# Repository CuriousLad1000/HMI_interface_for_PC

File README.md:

# HMI interface for PC

## Introduction

Personal Computers have become an integral part of our lives that even thinking about living without one would give us the feeling of falling back into stone age.

The idea behind this project was to build a smart Human Machine Interface for my personal computer. This project provided me with the opportunity of honing my skills while exploring various other domains. This project required technical expertise from different fields of technology including Electronics, Computer Science and Mechanical.

## Project Objective

The HMI interface will provide some advanced functionalities such as auto boot and shutdown, Automatic Temperature controller, vent controller, Lighting controller etc…

The project will involve some custom hardware designing, PCB fabrication, UX Designing, firmware programming, some mechanical designing and assembly using Rapid prototyping machines.

## Hardware/components used (not exhaustive list)

-   Arduino MEGA
-   3.5-inch Touch panel from Nextion
-   DC to DC Buck-Boost drivers
-   Mosfets (IRF510)
-   various passive components
-   Acryllic and MDF for casing and PC cabinet casing.
-   Laser cutter
-   CNC milling machine

## Software used

-   Arduino IDE (C/C++)
-   Nextion Editor to program touch panel.
-   Adobe Photoshop for UI designing.
-   Corel draw for Case, side panel and vents designing.
-   Cadsoft Eagle for PCB designing
-   Roland’s software and artcam for PCB fabrication (CNC milling).

##  Features offered

After completion, the HMI interface will have the following features.

-   Provide interactive system on/off switch
-   System Power on scheduler
-   Control the speed of fan based on conditions set.
    -   manual control of fan speed
    -   Automatic control based on the component’s temperature
-   Different Lighting modes for the system across multiple channels
    -   Rainbow
    -   Single color
    -   Fading on single color
    -   Rainbow cycle
    -   Color based on temperature
-   Display current temperature on multiple temperature gauges.
-   Provide settings for additional functionalities such as
    -   Open vents when system boots or based on the temperature -- servo control
    -   Enable power saver
    -   Enable/disable system status LED.
    -   Temperature channel assignment to various components.

<br/>

## Sample pictures (refer to wiki for more…)

<br/>

### HMI Interface

<br/>

**Home screen**

<p align="Center"> <i>"note: logo copyright belongs to Micro-Star INT'L CO., LTD" </i></p>

<br/>
<br/>

**Set Lighting modes**

<br/>
<br/>

**Temperature monitor**

<br/>
<br/>

## Device pics

<br/>
<br/>

**HMI Installed**

<br/>
<br/>

**HMI Operational**

<br/>
<br/>

> Check out wiki for more pics

<br/>
<br/>

### Video

<br/>
<br/>

**Device in action part-1**

<br/>
<br/>

**Device in action part-2**

<br/>

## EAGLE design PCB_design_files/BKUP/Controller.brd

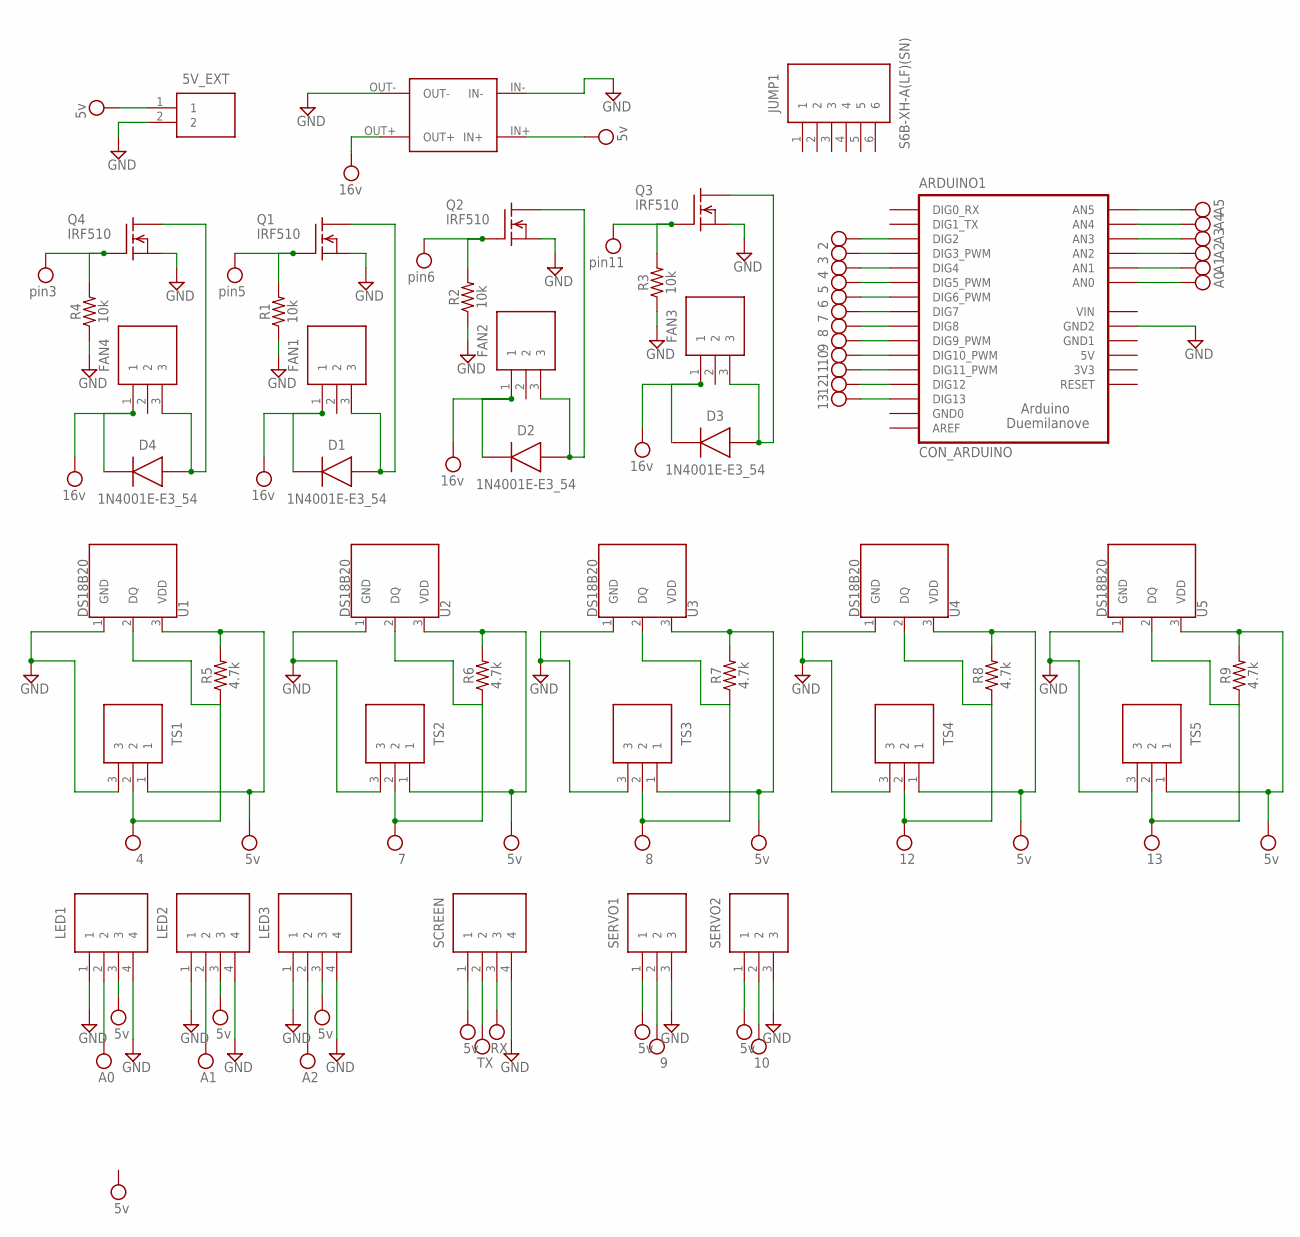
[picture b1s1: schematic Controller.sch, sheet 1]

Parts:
5V_EXT: S2B-XH-A(LF)(SN); SHDR2W80P0X250_1X2_740X575X700
ARDUINO1: CON_ARDUINO
D1, D2, D3, D4: 1N4001E-E3_54; DIOAD1405W86L465D235
FAN1, FAN2, FAN3, FAN4: S3B-XH-A(LF)(SN); SHDR3W80P0X250_1X3_990X610X700
JUMP1: S6B-XH-A(LF)(SN); SHDR6W64P0X250_1X6_1740X1155X7
LED1, LED2, LED3: S4B-XH-A(LF)(SN); SHDR4W64P0X250_1X4_1240X1155X7
Q1, Q2, Q3, Q4: IRF510; TO220
R1, R2, R3, R4: 10k; AXIAL-0.3
R5, R6, R7, R8, R9: 4.7k; AXIAL-0.3
SCREEN: S4B-XH-A(LF)(SN); SHDR4W64P0X250_1X4_1240X1155X7
SERVO1, SERVO2: S3B-XH-A(LF)(SN); SHDR3W80P0X250_1X3_990X610X700
TS1, TS2, TS3, TS4, TS5: S3B-XH-A(LF)(SN); SHDR3W80P0X250_1X3_990X610X700
U1, U2, U3, U4, U5: DS18B20; TO-92-AMMO
U$1: CN6009THROUGH_HOLE; CN6009

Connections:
5V_EXT: 5V_EXT.1, LED1.3, LED2.3, LED3.3, R5.P$2 (2), R6.P$2 (2), R7.P$2 (2), R8.P$2 (2), R9.P$2 (2), SCREEN.1, SERVO1.1, SERVO2.1, TS1.1, TS2.1, TS3.1, TS4.1, TS5.1, U1.3 (VDD), U2.3 (VDD), U3.3 (VDD), U4.3 (VDD), U5.3 (VDD), U$1.IN+; also elsewhere on the board
16V: D1.2 (K), D2.2 (K), D3.2 (K), D4.2 (K), FAN1.1, FAN2.1, FAN3.1, FAN4.1, U$1.OUT+; also elsewhere on the board
GND: 5V_EXT.2, ARDUINO1.GND2, LED1.1, LED1.4, LED2.1, LED2.4, LED3.1, LED3.4, Q1.3 (S), Q2.3 (S), Q3.3 (S), Q4.3 (S), R1.P$1 (1), R2.P$1 (1), R3.P$1 (1), R4.P$1 (1), SCREEN.4, SERVO1.3, SERVO2.3, TS1.3, TS2.3, TS3.3, TS4.3, TS5.3, U1.1 (GND), U2.1 (GND), U3.1 (GND), U4.1 (GND), U5.1 (GND), U$1.IN-, U$1.OUT-; also elsewhere on the board
unnamed: D2.1 (A), FAN2.3, Q2.2 (D)
unnamed: D3.1 (A), FAN3.3, Q3.2 (D)
unnamed: D1.1 (A), FAN1.3, Q1.2 (D)
unnamed: D4.1 (A), FAN4.3, Q4.2 (D)
PIN2: ARDUINO1.D_2 (DIG2)
PIN3: ARDUINO1.D_3 (DIG3_PWM), Q4.1 (G), R4.P$2 (2); also elsewhere on the board
PIN4: ARDUINO1.D_4 (DIG4), R5.P$1 (1), TS1.2, U1.2 (DQ)
PIN5: ARDUINO1.D_5 (DIG5_PWM), Q1.1 (G), R1.P$2 (2); also elsewhere on the board
PIN6: ARDUINO1.D_6 (DIG6_PWM), Q2.1 (G), R2.P$2 (2); also elsewhere on the board
PIN7: ARDUINO1.D_7 (DIG7), R6.P$1 (1), TS2.2, U2.2 (DQ)
PIN8: ARDUINO1.D_8 (DIG8), R7.P$1 (1), TS3.2, U3.2 (DQ)
PIN9: ARDUINO1.D_9 (DIG9_PWM), SERVO1.2
PIN10: ARDUINO1.D_10 (DIG10_PWM), SERVO2.2
PIN11: ARDUINO1.D_11 (DIG11_PWM), Q3.1 (G), R3.P$2 (2); also elsewhere on the board
PIN12: ARDUINO1.D_12 (DIG12), R8.P$1 (1), TS4.2, U4.2 (DQ)
PIN13: ARDUINO1.D_13 (DIG13), R9.P$1 (1), TS5.2, U5.2 (DQ)
PIN_A0: ARDUINO1.A_0 (AN0), LED1.2
PIN_A1: ARDUINO1.A_1 (AN1), LED2.2
PIN_A2: ARDUINO1.A_2 (AN2), LED3.2
PIN_A3: ARDUINO1.A_3 (AN3), SCREEN.2
PIN_A4: ARDUINO1.A_4 (AN4), SCREEN.3
PIN_A5: ARDUINO1.A_5 (AN5)
VIN: ARDUINO1.VIN

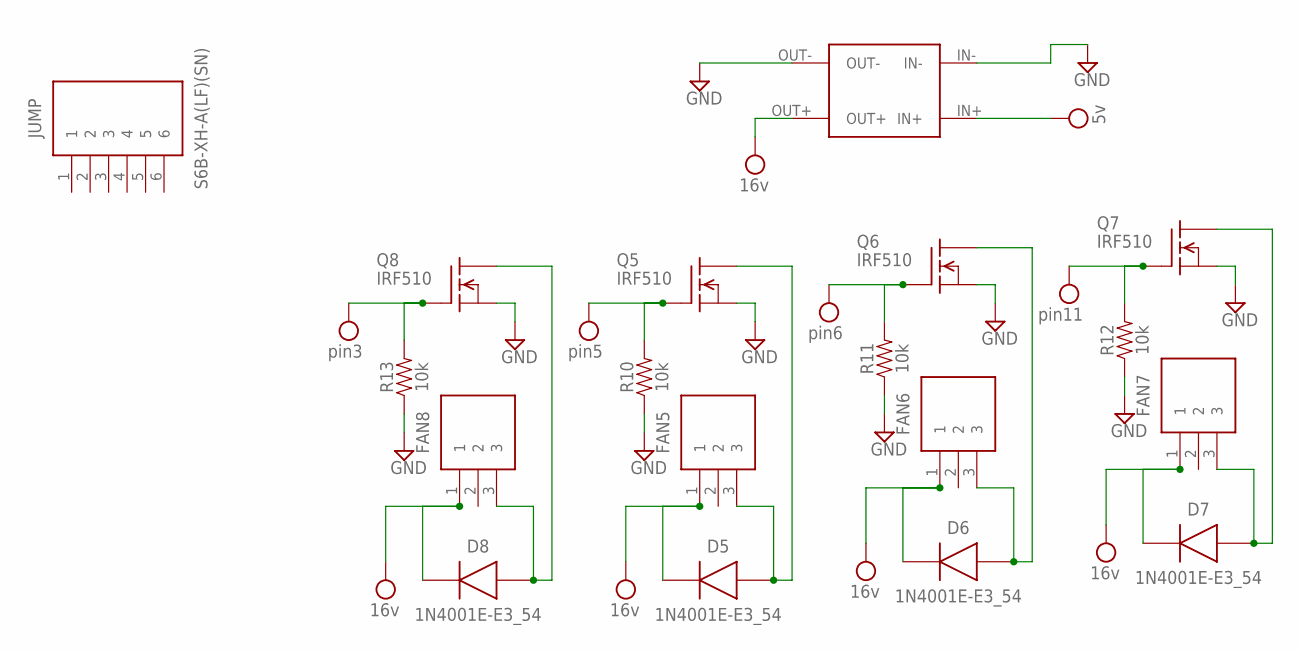
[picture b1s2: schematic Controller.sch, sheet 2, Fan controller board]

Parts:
D5, D6, D7, D8: 1N4001E-E3_54; DIOAD1405W86L465D235
FAN5, FAN6, FAN7, FAN8: S3B-XH-A(LF)(SN); SHDR3W80P0X250_1X3_990X610X700
JUMP: S6B-XH-A(LF)(SN); SHDR6W64P0X250_1X6_1740X1155X7
Q5, Q6, Q7, Q8: IRF510; TO220
R10, R11, R12, R13: 10k; AXIAL-0.3
U$2: CN6009THROUGH_HOLE; CN6009

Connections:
5V_EXT: U$2.IN+; also elsewhere on the board
16V: D5.2 (K), D6.2 (K), D7.2 (K), D8.2 (K), FAN5.1, FAN6.1, FAN7.1, FAN8.1, U$2.OUT+; also elsewhere on the board
GND: Q5.3 (S), Q6.3 (S), Q7.3 (S), Q8.3 (S), R10.P$1 (1), R11.P$1 (1), R12.P$1 (1), R13.P$1 (1), U$2.IN-, U$2.OUT-; also elsewhere on the board
unnamed: D5.1 (A), FAN5.3, Q5.2 (D)
unnamed: D6.1 (A), FAN6.3, Q6.2 (D)
unnamed: D7.1 (A), FAN7.3, Q7.2 (D)
unnamed: D8.1 (A), FAN8.3, Q8.2 (D)
PIN3: Q8.1 (G), R13.P$2 (2); also elsewhere on the board
PIN5: Q5.1 (G), R10.P$2 (2); also elsewhere on the board
PIN6: Q6.1 (G), R11.P$2 (2); also elsewhere on the board
PIN11: Q7.1 (G), R12.P$2 (2); also elsewhere on the board

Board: 2 copper layers, 59 parts (0 on the bottom side), 27 nets, no tracks yet.

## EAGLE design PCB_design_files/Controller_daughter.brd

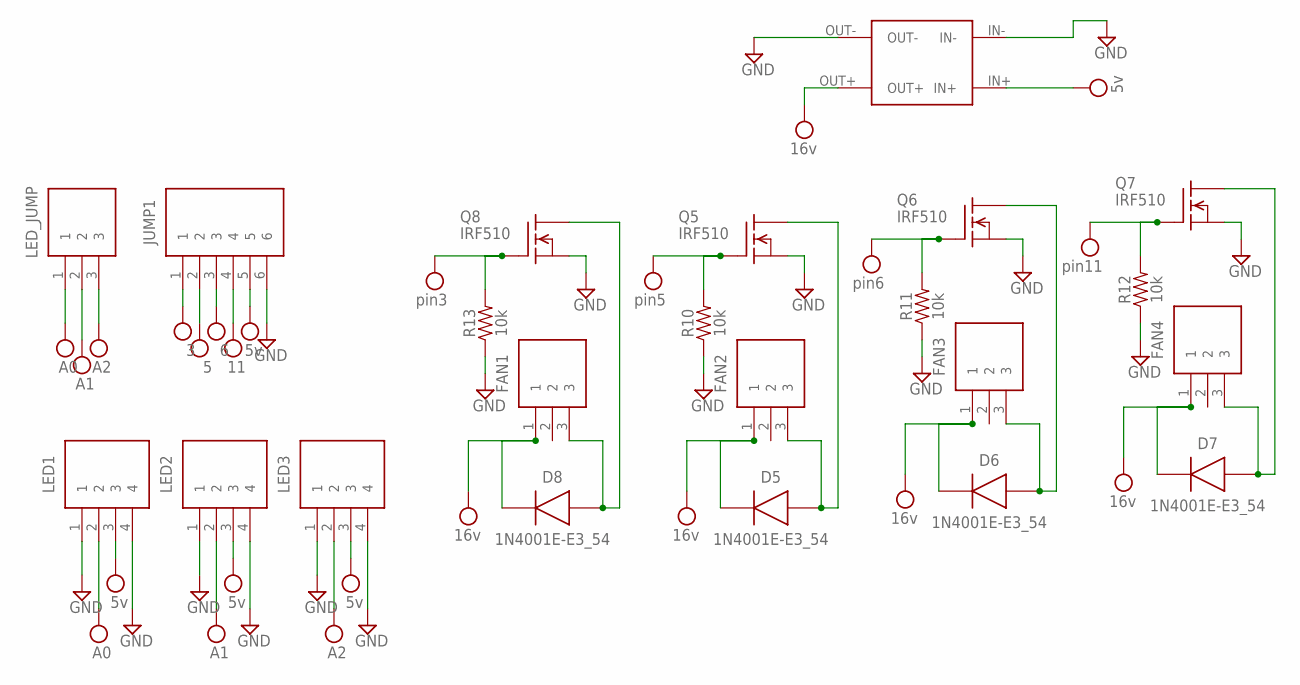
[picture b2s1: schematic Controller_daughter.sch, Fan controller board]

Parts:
D5, D6, D7, D8: 1N4001E-E3_54; DIOAD1405W86L465D235
FAN1, FAN2, FAN3, FAN4: S3B-XH-A(LF)(SN); SHDR3W80P0X250_1X3_990X610X700
JUMP1: S6B-XH-A(LF)(SN); SHDR6W64P0X250_1X6_1740X1155X7
LED1, LED2, LED3: S4B-XH-A(LF)(SN); SHDR4W64P0X250_1X4_1240X1155X7
LED_JUMP: S3B-XH-A(LF)(SN); SHDR3W80P0X250_1X3_990X610X700
Q5, Q6, Q7, Q8: IRF510; TO220
R10, R11, R12, R13: 10k; AXIAL-0.3
U$2: CN6009THROUGH_HOLE; CN6009

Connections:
5V_EXT: JUMP1.5, LED1.3, LED2.3, LED3.3, U$2.IN+
16V: D5.2 (K), D6.2 (K), D7.2 (K), D8.2 (K), FAN1.1, FAN2.1, FAN3.1, FAN4.1, U$2.OUT+
GND: JUMP1.6, LED1.1, LED1.4, LED2.1, LED2.4, LED3.1, LED3.4, U$2.IN-
GND_16: Q5.3 (S), Q6.3 (S), Q7.3 (S), Q8.3 (S), R10.P$1 (1), R11.P$1 (1), R12.P$1 (1), R13.P$1 (1), U$2.OUT-
unnamed: D5.1 (A), FAN2.3, Q5.2 (D)
unnamed: D6.1 (A), FAN3.3, Q6.2 (D)
unnamed: D7.1 (A), FAN4.3, Q7.2 (D)
unnamed: D8.1 (A), FAN1.3, Q8.2 (D)
PIN3: JUMP1.1, Q8.1 (G), R13.P$2 (2)
PIN5: JUMP1.2, Q5.1 (G), R10.P$2 (2)
PIN6: JUMP1.3, Q6.1 (G), R11.P$2 (2)
PIN11: JUMP1.4, Q7.1 (G), R12.P$2 (2)
PIN_A0: LED1.2, LED_JUMP.1
PIN_A1: LED2.2, LED_JUMP.2
PIN_A2: LED3.2, LED_JUMP.3

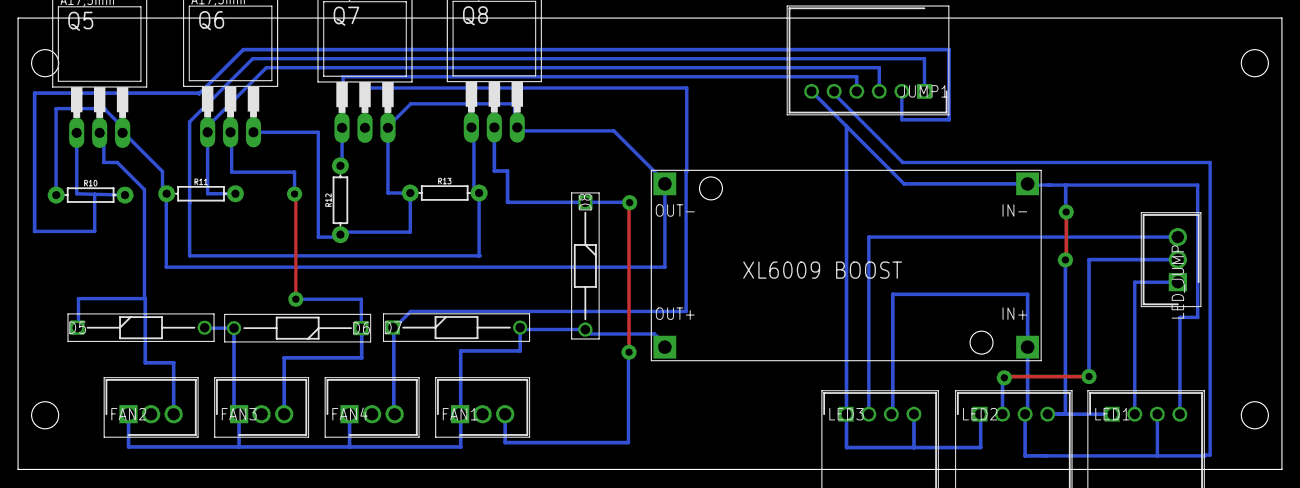
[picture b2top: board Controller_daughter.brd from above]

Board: 2 copper layers, 140.0 x 50.0 mm, 22 parts (0 on the bottom side), 15 nets.

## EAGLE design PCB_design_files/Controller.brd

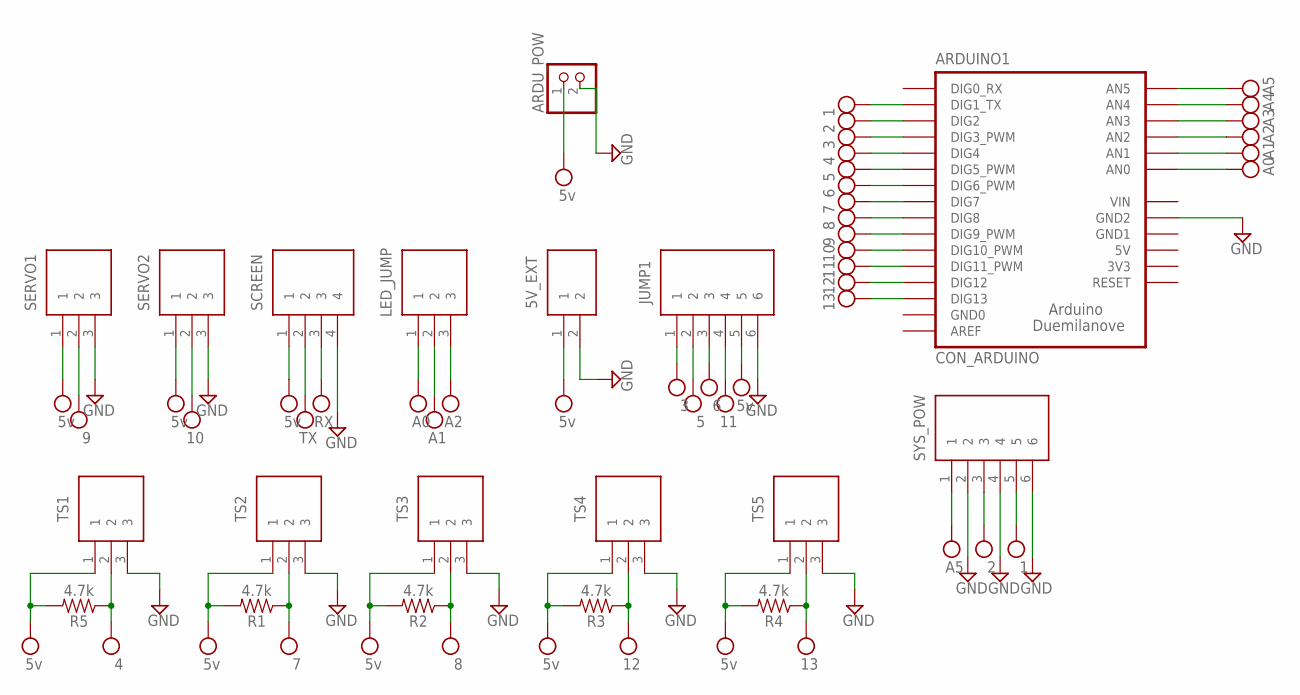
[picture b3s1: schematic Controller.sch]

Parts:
5V_EXT: S2B-XH-A(LF)(SN); SHDR2W80P0X250_1X2_740X575X700
ARDUINO1: CON_ARDUINO
ARDU_POW: PINHD-1X2; 1X02
JUMP1: S6B-XH-A(LF)(SN); SHDR6W64P0X250_1X6_1740X1155X7
LED_JUMP: S3B-XH-A(LF)(SN); SHDR3W80P0X250_1X3_990X610X700
R1, R2, R3, R4, R5: 4.7k; AXIAL-0.3
SCREEN: S4B-XH-A(LF)(SN); SHDR4W64P0X250_1X4_1240X1155X7
SERVO1, SERVO2: S3B-XH-A(LF)(SN); SHDR3W80P0X250_1X3_990X610X700
SYS_POW: S6B-XH-A(LF)(SN); SHDR6W64P0X250_1X6_1740X1155X7
TS1, TS2, TS3, TS4, TS5: S3B-XH-A(LF)(SN); SHDR3W80P0X250_1X3_990X610X700

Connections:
5V_EXT: 5V_EXT.1, ARDU_POW.1, JUMP1.5, R1.P$2 (2), R2.P$2 (2), R3.P$2 (2), R4.P$2 (2), R5.P$2 (2), SCREEN.1, SERVO1.1, SERVO2.1, TS1.1, TS2.1, TS3.1, TS4.1, TS5.1
GND: 5V_EXT.2, ARDUINO1.GND2, ARDU_POW.2, JUMP1.6, SCREEN.4, SERVO1.3, SERVO2.3, SYS_POW.2, SYS_POW.4, SYS_POW.6, TS1.3, TS2.3, TS3.3, TS4.3, TS5.3
PIN1: ARDUINO1.D_1 (DIG1_TX), SYS_POW.5
PIN2: ARDUINO1.D_2 (DIG2), SYS_POW.3
PIN3: ARDUINO1.D_3 (DIG3_PWM), JUMP1.1
PIN4: ARDUINO1.D_4 (DIG4), R5.P$1 (1), TS1.2
PIN5: ARDUINO1.D_5 (DIG5_PWM), JUMP1.2
PIN6: ARDUINO1.D_6 (DIG6_PWM), JUMP1.3
PIN7: ARDUINO1.D_7 (DIG7), R1.P$1 (1), TS2.2
PIN8: ARDUINO1.D_8 (DIG8), R2.P$1 (1), TS3.2
PIN9: ARDUINO1.D_9 (DIG9_PWM), SERVO1.2
PIN10: ARDUINO1.D_10 (DIG10_PWM), SERVO2.2
PIN11: ARDUINO1.D_11 (DIG11_PWM), JUMP1.4
PIN12: ARDUINO1.D_12 (DIG12), R3.P$1 (1), TS4.2
PIN13: ARDUINO1.D_13 (DIG13), R4.P$1 (1), TS5.2
PIN_A0: ARDUINO1.A_0 (AN0), LED_JUMP.1
PIN_A1: ARDUINO1.A_1 (AN1), LED_JUMP.2
PIN_A2: ARDUINO1.A_2 (AN2), LED_JUMP.3
PIN_A3: ARDUINO1.A_3 (AN3), SCREEN.2
PIN_A4: ARDUINO1.A_4 (AN4), SCREEN.3
PIN_A5: ARDUINO1.A_5 (AN5), SYS_POW.1
VIN: ARDUINO1.VIN

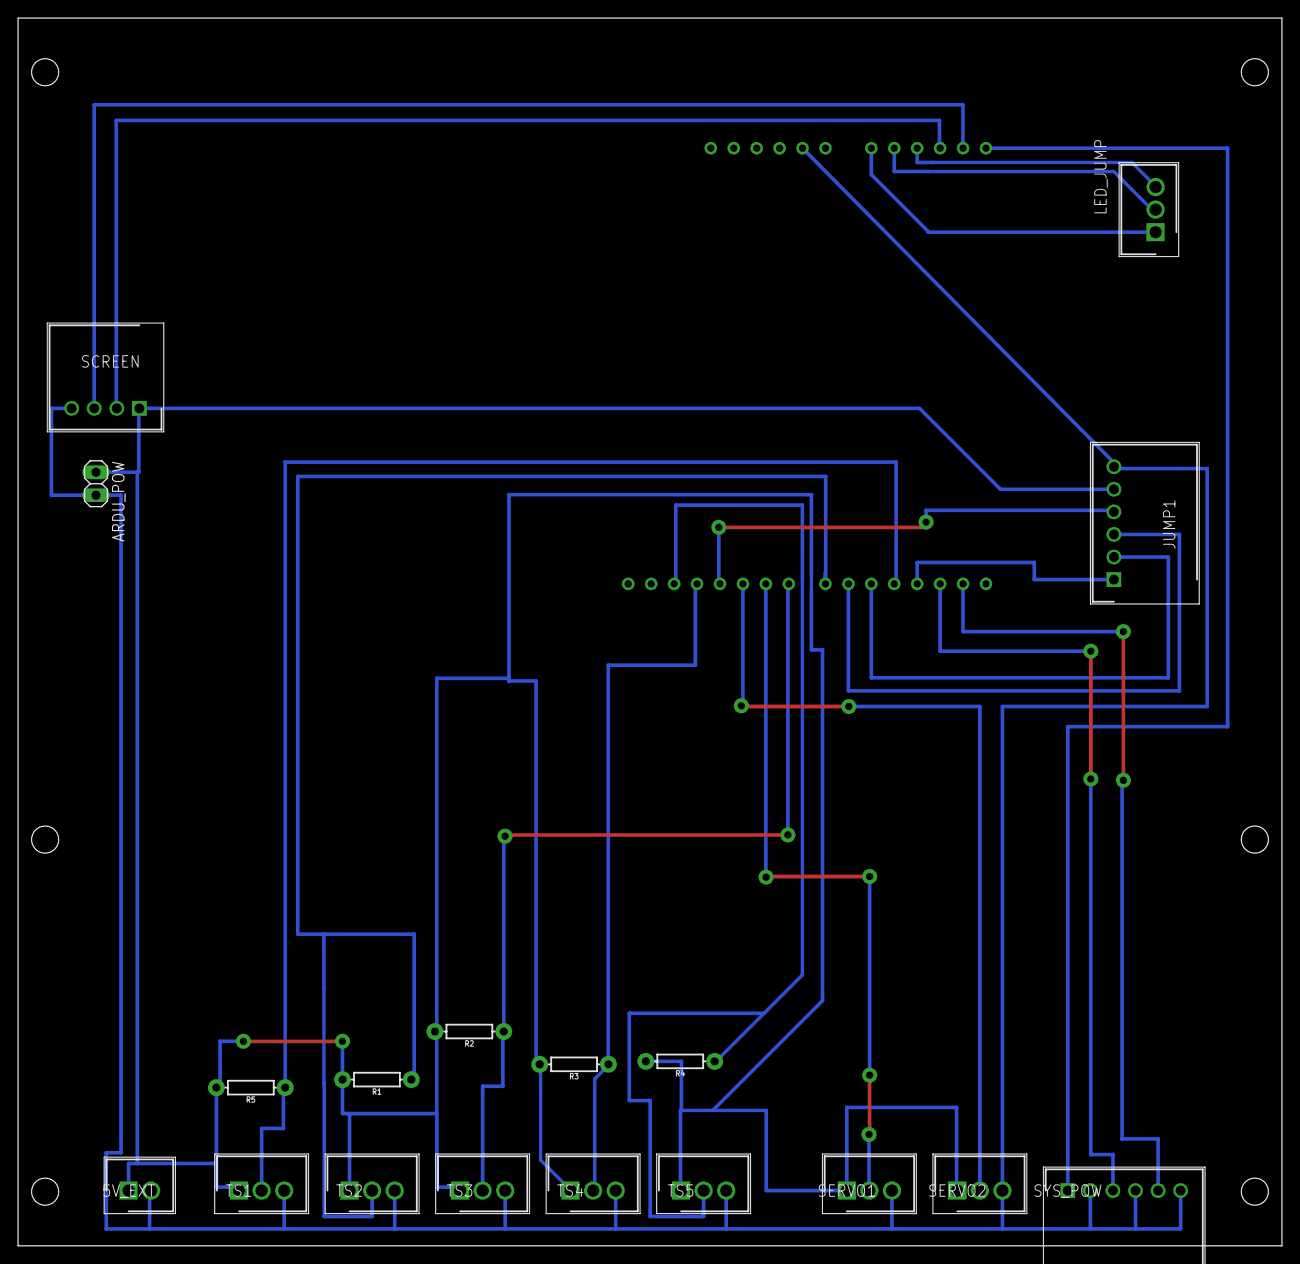
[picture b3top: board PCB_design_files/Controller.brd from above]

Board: 2 copper layers, 140.0 x 136.0 mm, 19 parts (1 on the bottom side), 21 nets.

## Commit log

2022-06-07 Readme updated
    Overview and pics added
2022-06-07 Fixed links
    Formatted the doc
    Fixed image links
    added videos
2022-06-07 Update 'README.md'
2022-06-07 Controller code ver. 1.0
    14 Dec 2017
2022-06-07 controller code ver. 1.1
    17 Dec 2017
2022-06-07 Controller code ver. 1.2
    24 Dec 2017
2022-06-07 Added test code snippets
    These codes were sued for testing and debugging the project.
2022-06-07 HMI code ver. 1.0
    Controller HMI 8-dec-17
2022-06-07 HMI code ver. 1.1
    Controller HMI 9-dec-17
2022-06-07 HMI code ver. 2.0
    Controller HMI 14-dec-17
2022-06-07 HMI code ver. 2.1
    Controller HMI 16-dec-17
2022-06-07 UI Design Resources
2022-06-07 PCB design files
    board and schematic files for main and daughter board.

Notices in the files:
parts and their libraries:
SparkFun-Resistors: Licensing: Creative Commons ShareAlike 4.0 International - https://creativecommons.org/licenses/by-sa/4.0
